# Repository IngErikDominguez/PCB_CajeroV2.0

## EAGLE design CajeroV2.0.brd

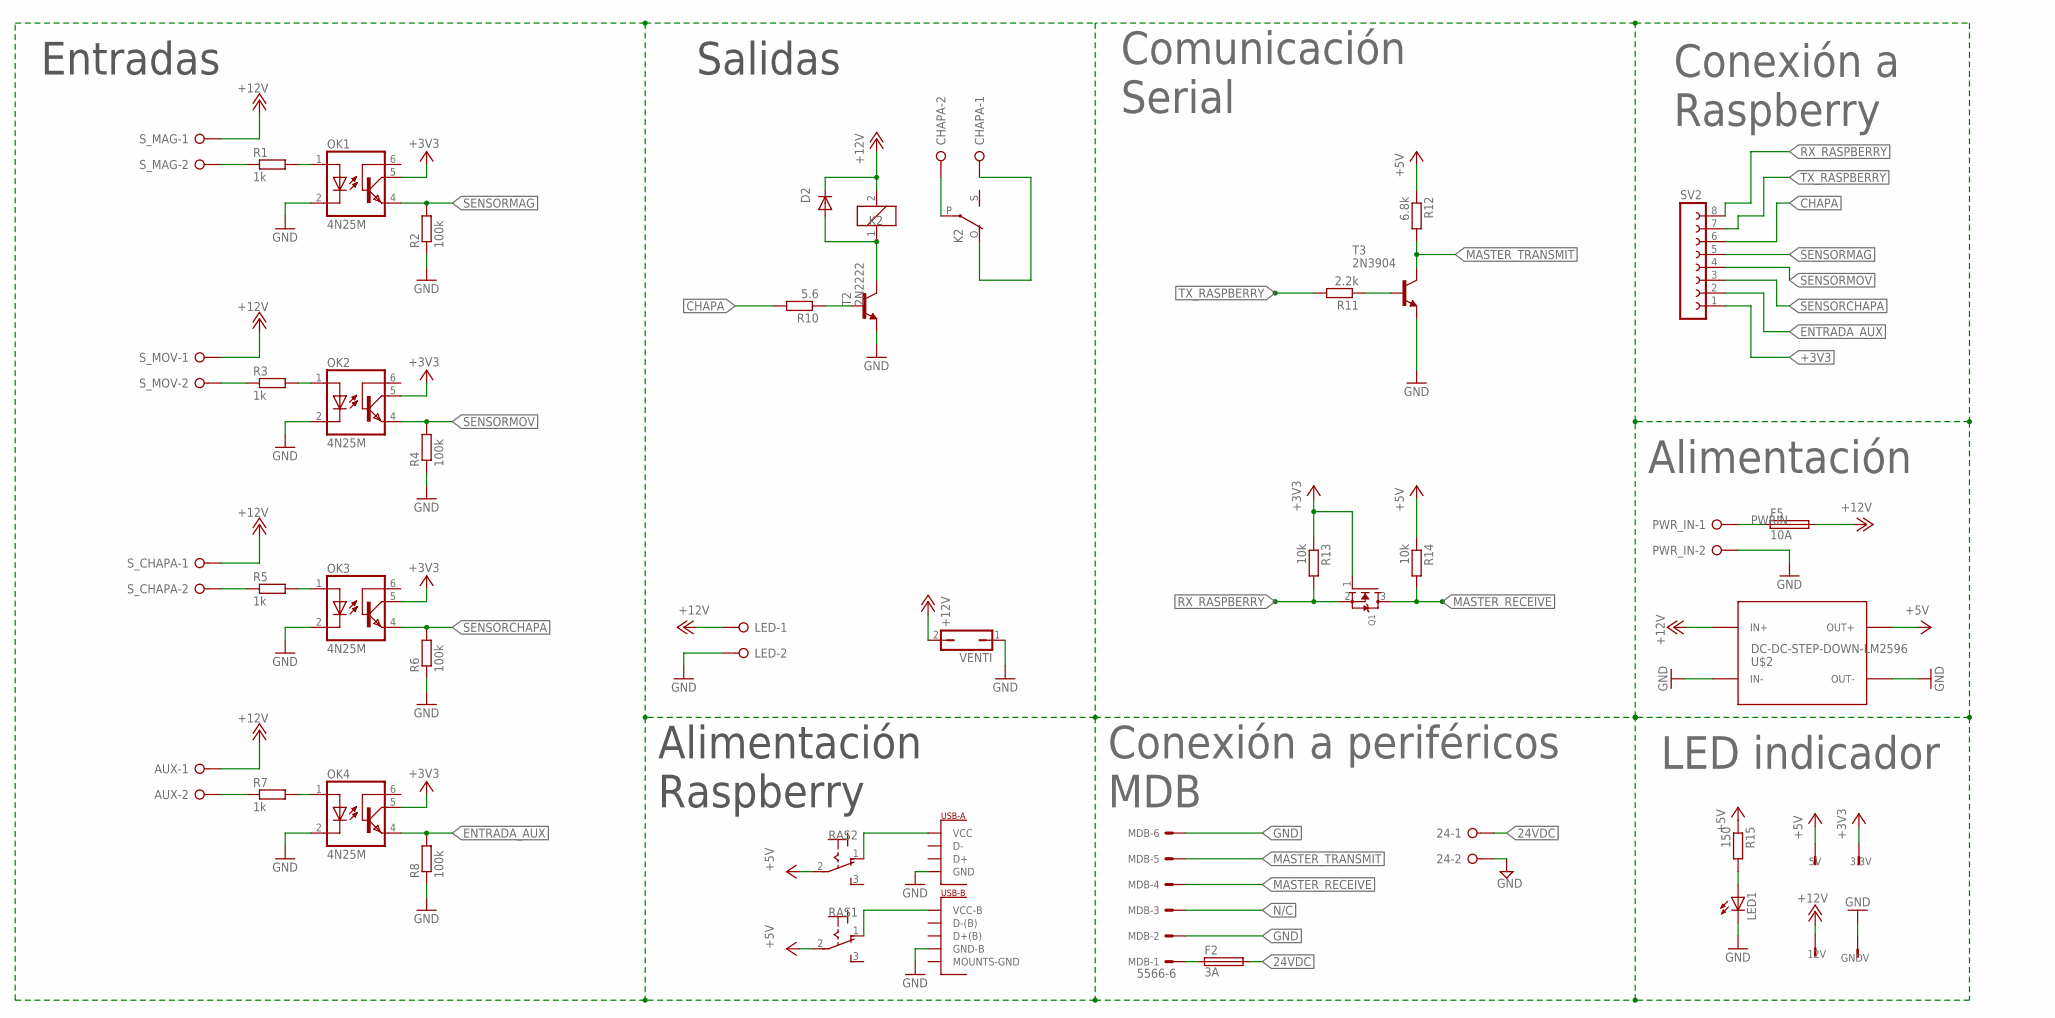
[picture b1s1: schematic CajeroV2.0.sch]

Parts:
3.3V, 5V, 12V: TSW-101-07-G-S; TSW-101-XX-G-S
24: W237-02P; W237-132
AUX: W237-02P; W237-132
CHAPA: W237-02P; W237-132
D2: 1N4148DO35-10; DO35-10
F2: 3A; SHK20L
F5: 10A; SHK20L
GNDV: TSW-101-07-G-S; TSW-101-XX-G-S
K2: G5LE
LED: W237-02P; W237-132
LED1: LED5MM
MDB: 5566-6
OK1, OK2, OK3, OK4: 4N25M; DIL06
PWR_IN: W237-02P; W237-132
Q1: MOSFET-NREFLOW; SOT23
R1, R3, R5, R7: 1k; 0207/7
R2, R4, R6, R8: 100k; 0207/7
R10: 5.6; 0207/7
R11: 2.2k; 0207/7
R12: 6.8k; 0207/7
R13, R14: 10k; 0207/7
R15: 150; 0207/7
RAS1, RAS2: 320-916
SV2: FE08-1; FE08
S_CHAPA: W237-02P; W237-132
S_MAG: W237-02P; W237-132
S_MOV: W237-02P; W237-132
T2: 2N2222; TO18
T3: 2N3904; TO92
U$1: DUAL-PORT-USB-REC; DUAL-PORT-USB
U$2: DC-DC-STEP-DOWN-LM2596
VENTI: JP1Q; JP1

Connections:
24VDC: 24.1, F2.2A
+3V3: 3.3V.1, OK1.5 (COL), OK2.5 (COL), OK3.5 (COL), OK4.5 (COL), Q1.1 (G), R13.1, SV2.1
+5V: 5V.1, R12.1, R14.1, R15.1, RAS1.2, RAS2.2, U$2.OUT+
+12V: 12V.1, AUX.1, D2.C, F5.2A, K2.2, LED.1, S_CHAPA.1, S_MAG.1, S_MOV.1, U$2.IN+, VENTI.2
CHAPA: R10.2, SV2.6
ENTRADA_AUX: OK4.4 (EMI), R8.2, SV2.2
GND: 24.2, GNDV.1, LED.2, LED1.K (C), MDB.2, MDB.6, OK1.2 (C), OK2.2 (C), OK3.2 (C), OK4.2 (C), PWR_IN.2, R2.1, R4.1, R6.1, R8.1, T2.1 (E), T3.3 (E), U$1.P$9 (GND-B), U$1.P$11 (GND), U$2.IN-, U$2.OUT-, VENTI.1
MASTER_RECEIVE: MDB.4, Q1.3 (D), R14.2
MASTER_TRANSMIT: MDB.5, R12.2, T3.1 (C)
MOUNTS-GND: U$1.GND (MOUNTS-GND), U$1.P$2 (MOUNTS-GND), U$1.P$3 (MOUNTS-GND), U$1.P$4 (MOUNTS-GND)
unnamed: OK1.1 (A), R1.2
unnamed: R1.1, S_MAG.2
unnamed: OK2.1 (A), R3.2
unnamed: R3.1, S_MOV.2
unnamed: OK3.1 (A), R5.2
unnamed: R5.1, S_CHAPA.2
unnamed: OK4.1 (A), R7.2
unnamed: AUX.2, R7.1
unnamed: R10.1, T2.2 (B)
unnamed: D2.A, K2.1, T2.3 (C)
unnamed: CHAPA.2, K2.P
unnamed: CHAPA.1, K2.O
unnamed: R11.1, T3.2 (B)
unnamed: RAS2.1 (O), U$1.P$12 (VCC)
unnamed: F2.1A, MDB.1
unnamed: LED1.A, R15.2
unnamed: RAS1.1 (O), U$1.P$10 (VCC-B)
N/C: MDB.3
PWRIN: F5.1A, PWR_IN.1
RX_RASPBERRY: Q1.2 (S), R13.2, SV2.8
SENSORCHAPA: OK3.4 (EMI), R6.2, SV2.3
SENSORMAG: OK1.4 (EMI), R2.2, SV2.5
SENSORMOV: OK2.4 (EMI), R4.2, SV2.4
TX_RASPBERRY: R11.2, SV2.7

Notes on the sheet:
Entradas
Salidas
Alimentación Raspberry
Comunicación Serial
Conexión a periféricos MDB
Conexión a Raspberry
Alimentación
LED indicador

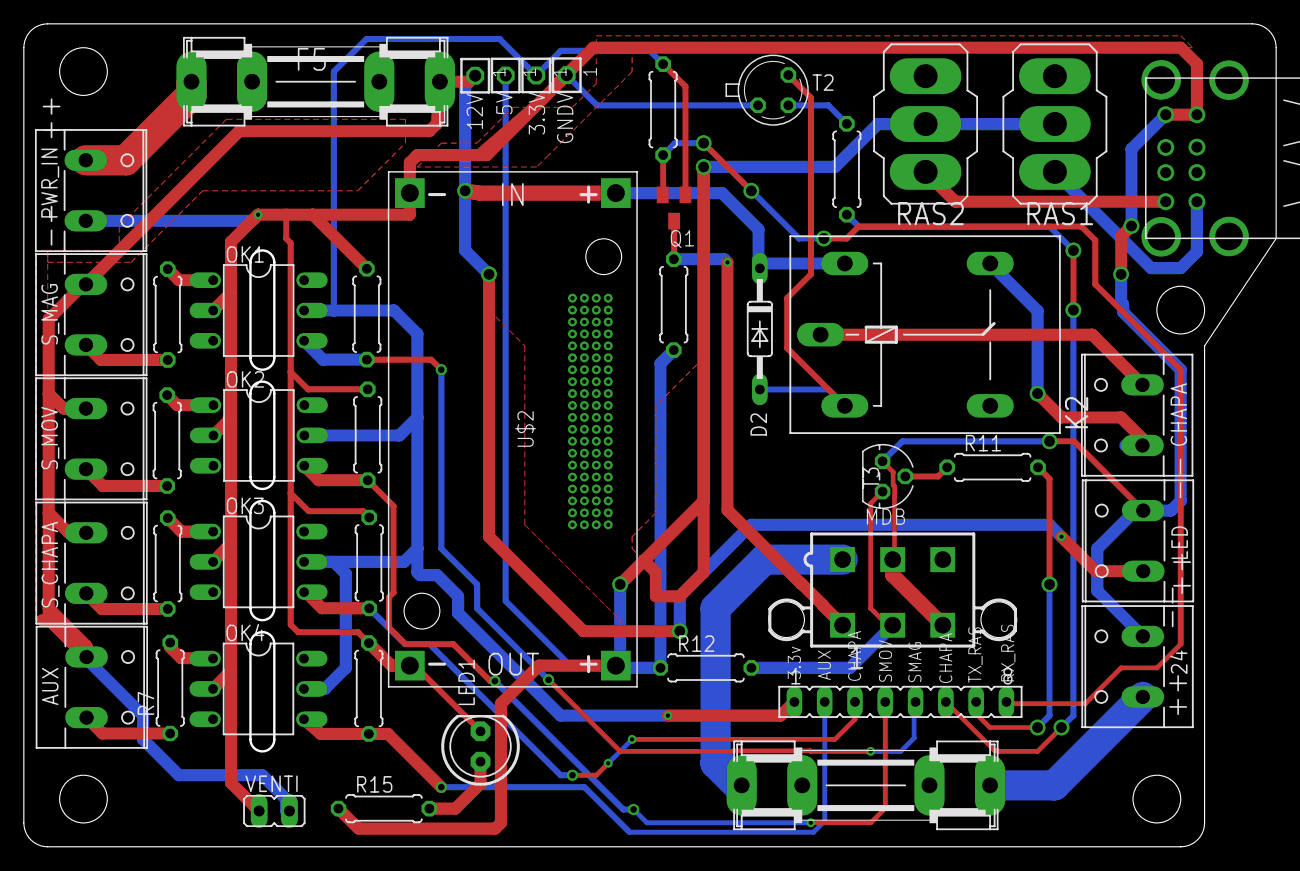
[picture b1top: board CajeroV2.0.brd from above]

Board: 2 copper layers, 104.8 x 68.8 mm, 45 parts (0 on the bottom side), 33 nets.

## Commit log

2019-01-31 V2.1
    Cambio de posición un fusible y arreglo overlap

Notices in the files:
parts and their libraries:
diy-modules: Released under the Creative Commons Attribution 4.0 International License: http://creativecommons.org/licenses/by/4.0
